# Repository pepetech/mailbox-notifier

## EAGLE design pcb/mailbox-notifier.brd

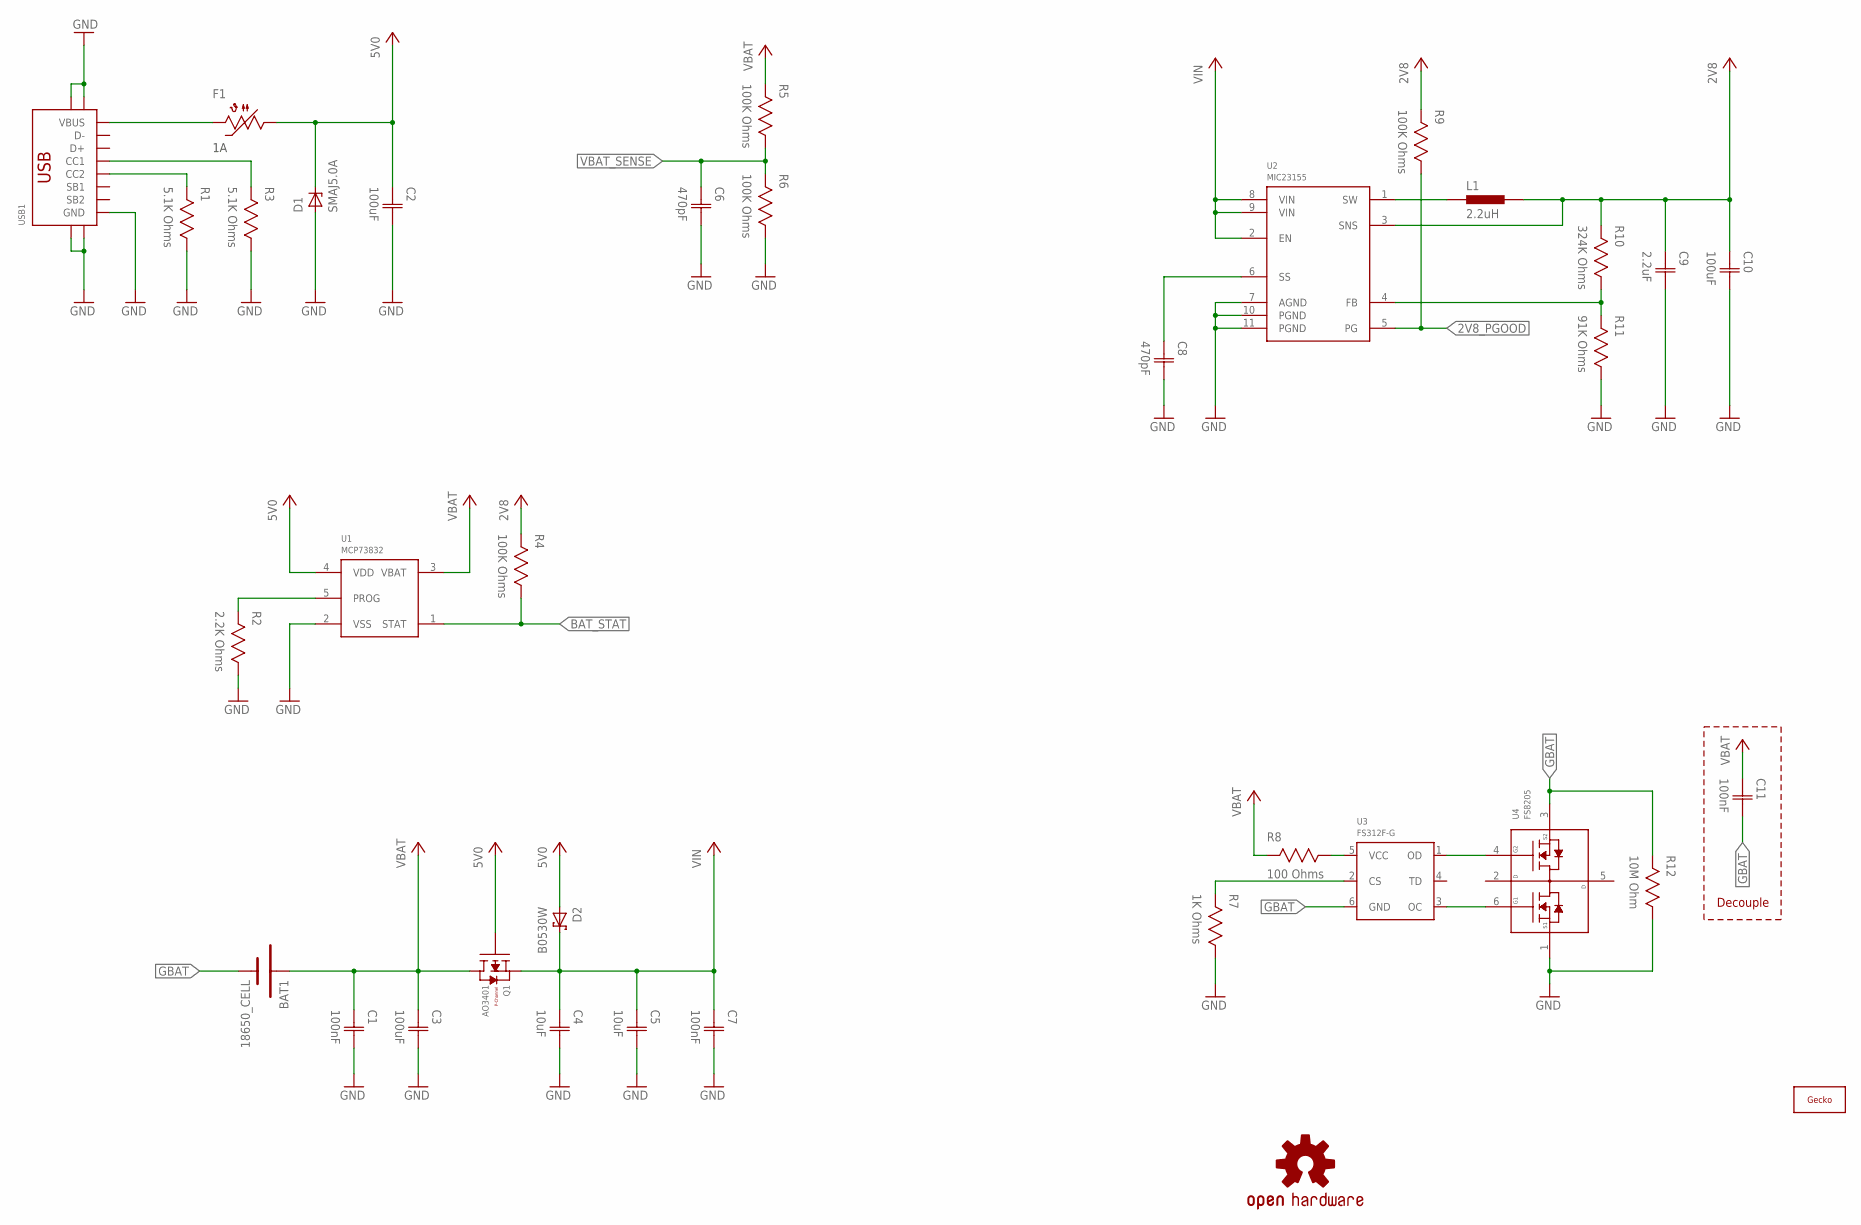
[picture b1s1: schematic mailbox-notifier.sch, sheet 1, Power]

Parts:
BAT1: 18650_CELL; 18650
C1, C7, C11: 100nF; CAP0603
C2, C3, C10: 100uF; CAP1206
C4, C5: 10uF; CAP0603
C6, C8: 470pF; CAP0603
C9: 2.2uF; CAP0603
D1: SMAJ5.0A; DO214AC
D2: B0530W; SOD-123
F1: 1A Hold; 1206
L1: 2.2uH; IND0805
LOGO1: GECKO-14MM; GECKO_14MM
LOGO2: OSHW-LOGOM; OSHW-LOGO-M
Q1: AO3401; SOT23
R1, R3: 5.1K Ohms; RES0603
R2: 2.2K Ohms; RES0603
R4, R5, R6, R9: 100K Ohms; RES0603
R7: 1K Ohms; RES0603
R8: 100 Ohms; RES0603
R10: 324K Ohms; RES0603
R11: 91K Ohms; RES0603
R12: 10M Ohm; RES0603
U1: MCP73832; SOT23-5
U2: MIC23155; DFN10
U3: FS312F-G; SOT23-6
U4: FS8205; SOT23-6
USB1: USB-C-16P-SMD-FLAT-SIDE-TYPE-2

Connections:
2V8: C9.1 (C1), C10.1 (C1), L1.2, R4.2, R9.2, R10.2, U2.3 (SNS); also elsewhere on the board
2V8_PGOOD: R9.1, U2.5 (PG); also elsewhere on the board
5V0: C2.1 (C1), D1.C, D2.A, F1.1, Q1.1 (G), U1.4 (VDD)
BAT_STAT: R4.1, U1.1 (STAT); also elsewhere on the board
GBAT: BAT1.-, C11.2 (C2), R12.2, U3.6 (GND), U4.3 (S2)
GND: C1.2 (C2), C2.2 (C2), C3.2 (C2), C4.2 (C2), C5.2 (C2), C6.2 (C2), C7.2 (C2), C8.2 (C2), C9.2 (C2), C10.2 (C2), D1.A, R1.1, R2.1, R3.1, R6.1, R7.1, R11.1, R12.1, U1.2 (VSS), U2.7 (AGND), U2.10 (PGND), U2.11 (PGND), U4.1 (S1), USB1.A1/B12 (GND), USB1.B1/A12 (GND), USB1.SHIELD@0 (SHIELD), USB1.SHIELD@1 (SHIELD), USB1.SHIELD@2 (SHIELD), USB1.SHIELD@3 (SHIELD); also elsewhere on the board
unnamed: R1.2, USB1.B5 (CC2)
unnamed: F1.2, USB1.A4/B9 (VBUS), USB1.B4/A9 (VBUS)
unnamed: R3.2, USB1.A5 (CC1)
unnamed: R2.2, U1.5 (PROG)
unnamed: L1.1, U2.1 (SW)
unnamed: R10.1, R11.2, U2.4 (FB)
unnamed: C8.1 (C1), U2.6 (SS)
unnamed: U3.3 (OC), U4.6 (G1)
unnamed: U3.1 (OD), U4.4 (G2)
unnamed: R8.1, U3.5 (VCC)
unnamed: R7.2, U3.2 (CS)
VBAT: BAT1.+, C1.1 (C1), C3.1 (C1), C11.1 (C1), Q1.3 (D), R5.2, R8.2, U1.3 (VBAT)
VBAT_SENSE: C6.1 (C1), R5.1, R6.2; also elsewhere on the board
VIN: C4.1 (C1), C5.1 (C1), C7.1 (C1), D2.C, Q1.2 (S), U2.2 (EN), U2.8 (VIN), U2.9 (VIN)

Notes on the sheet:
Decouple

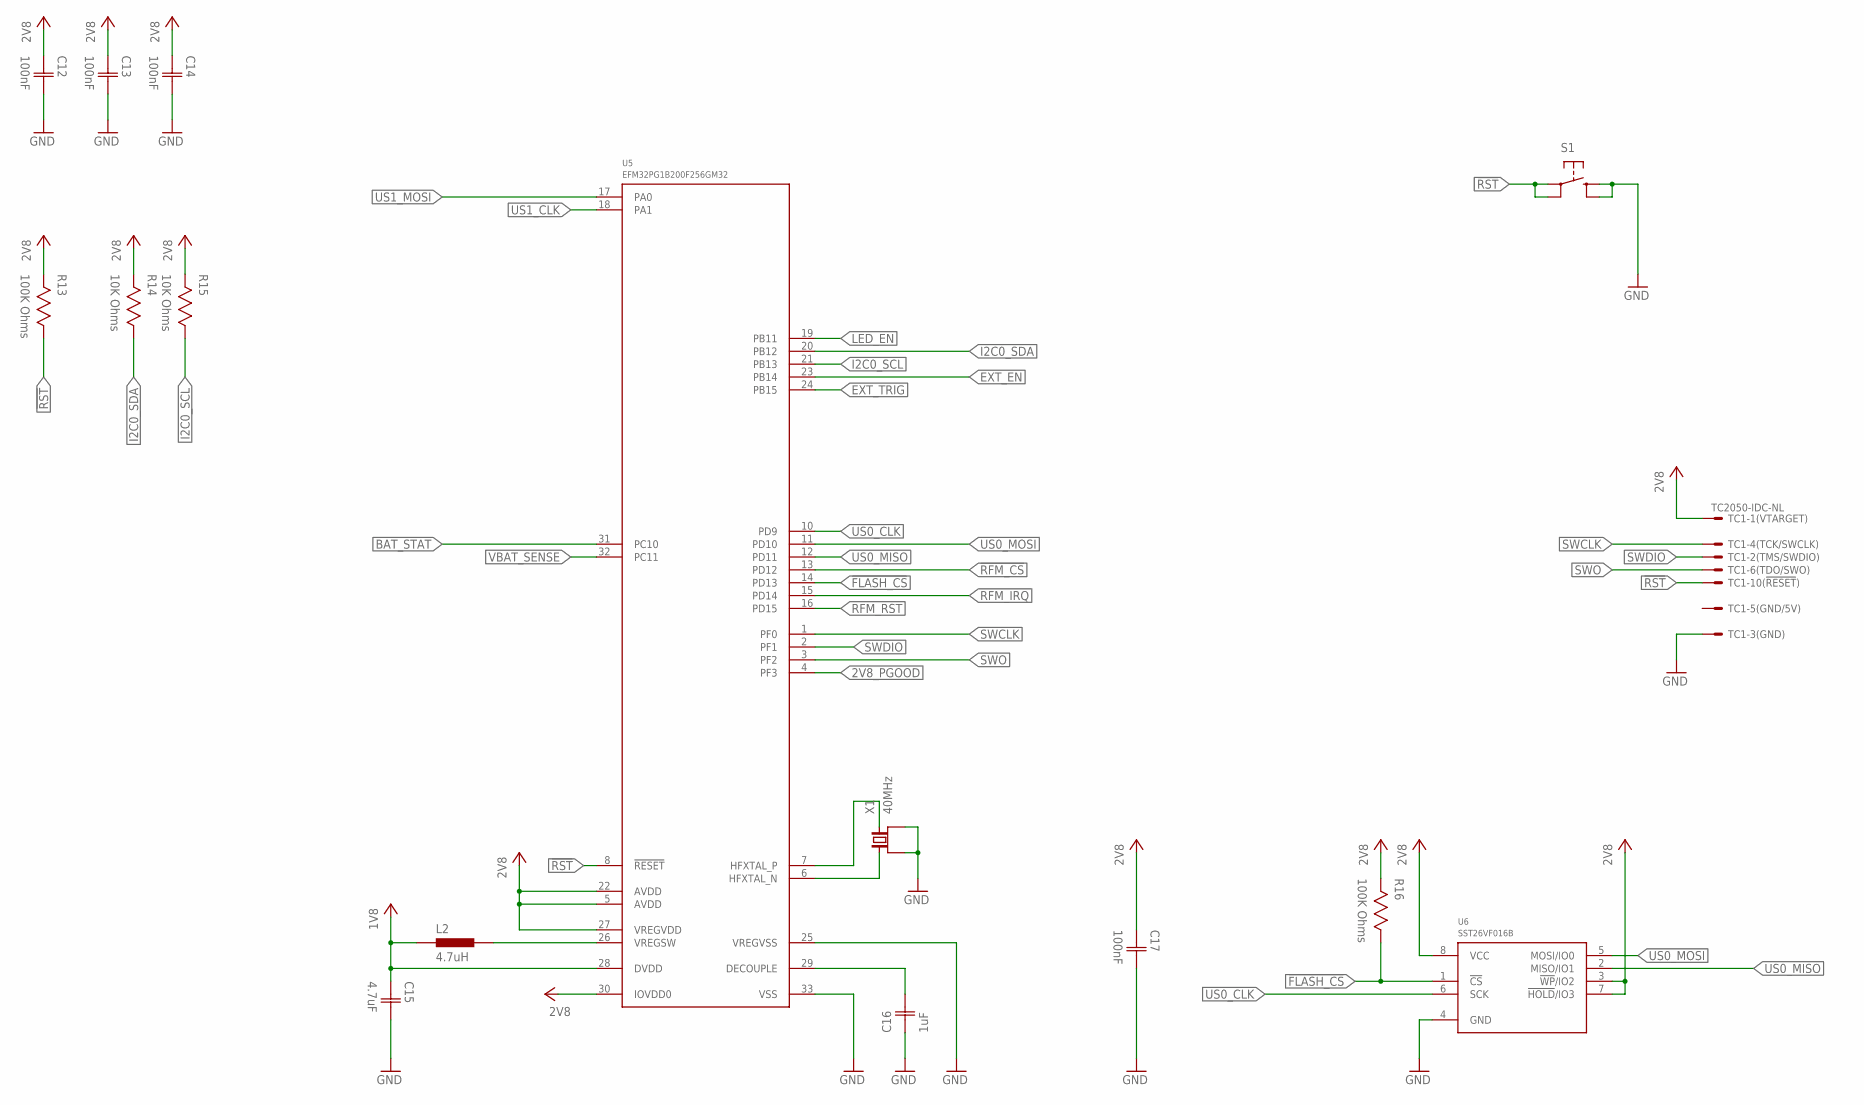
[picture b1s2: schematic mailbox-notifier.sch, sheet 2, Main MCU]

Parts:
C12, C13, C14, C17: 100nF; CAP0603
C15: 4.7uF; CAP0603
C16: 1uF; CAP0603
L2: 4.7uH; IND0603
R13, R16: 100K Ohms; RES0603
R14, R15: 10K Ohms; RES0603
S1: TAC_SWITCHSMD; TAC_SW_SMD_RESET
TC1: TC2050-IDC-NL
U5: EFM32PG1B200F256GM32; QFN32_0.5P
U6: SST26VF016B; WSOIC8
X1: 40MHz; 4-SMD-3225

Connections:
1V8: C15.1 (C1), L2.1, U5.28 (DVDD)
2V8: C12.1 (C1), C13.1 (C1), C14.1 (C1), C17.1 (C1), R13.2, R14.2, R15.2, R16.2, TC1.1, U5.5 (AVDD), U5.22 (AVDD), U5.27 (VREGVDD), U5.30 (IOVDD0), U6.3 (!WP!/IO2), U6.7 (!HOLD!/IO3), U6.8 (VCC); also elsewhere on the board
2V8_PGOOD: U5.4 (PF3); also elsewhere on the board
!FLASH_CS: R16.1, U5.14 (PD13), U6.1 (!CS!)
!RFM_CS: U5.13 (PD12); also elsewhere on the board
!RST: R13.1, S1.1, S1.2, TC1.10, U5.8 (!RESET)
BAT_STAT: U5.31 (PC10); also elsewhere on the board
EXT_EN: U5.23 (PB14); also elsewhere on the board
EXT_TRIG: U5.24 (PB15); also elsewhere on the board
GND: C12.2 (C2), C13.2 (C2), C14.2 (C2), C15.2 (C2), C16.1 (C1), C17.2 (C2), S1.3, S1.4, TC1.3, U5.25 (VREGVSS), U5.33 (VSS), U6.4 (GND), X1.1 (GND), X1.3 (GND); also elsewhere on the board
I2C0_SCL: R15.1, U5.21 (PB13); also elsewhere on the board
I2C0_SDA: R14.1, U5.20 (PB12); also elsewhere on the board
LED_EN: U5.19 (PB11); also elsewhere on the board
unnamed: U5.6 (HFXTAL_N), X1.2 (1)
unnamed: U5.7 (HFXTAL_P), X1.4 (2)
unnamed: L2.2, U5.26 (VREGSW)
unnamed: C16.2 (C2), U5.29 (DECOUPLE)
RFM_IRQ: U5.15 (PD14); also elsewhere on the board
RFM_RST: U5.16 (PD15); also elsewhere on the board
SWCLK: TC1.4, U5.1 (PF0)
SWDIO: TC1.2, U5.2 (PF1)
SWO: TC1.6, U5.3 (PF2)
US0_CLK: U5.10 (PD9), U6.6 (SCK); also elsewhere on the board
US0_MISO: U5.12 (PD11), U6.2 (MISO/IO1); also elsewhere on the board
US0_MOSI: U5.11 (PD10), U6.5 (MOSI/IO0); also elsewhere on the board
US1_CLK: U5.18 (PA1); also elsewhere on the board
US1_MOSI: U5.17 (PA0); also elsewhere on the board
VBAT_SENSE: U5.32 (PC11); also elsewhere on the board

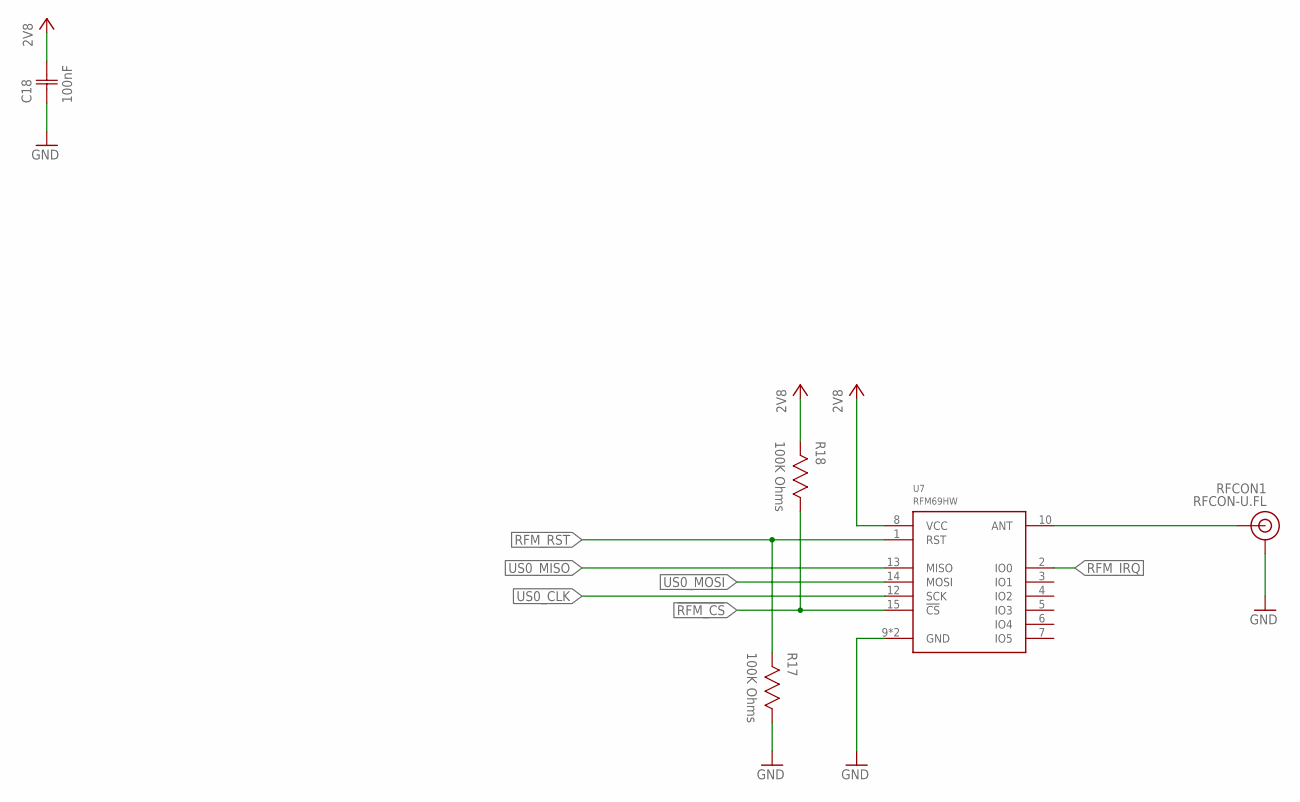
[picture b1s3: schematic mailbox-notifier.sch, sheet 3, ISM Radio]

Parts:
C18: 100nF; CAP0603
R17, R18: 100K Ohms; RES0603
RFCON1: RFCON-U.FL; U.FL
U7: RFM69HW; RFM69XW-XXXS2

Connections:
2V8: C18.2 (C2), R18.2, U7.8 (VCC); also elsewhere on the board
!RFM_CS: R18.1, U7.15 (!CS); also elsewhere on the board
GND: C18.1 (C1), R17.1, RFCON1.P$1 (GND), RFCON1.P$2 (GND), U7.9 (GND), U7.11 (GND); also elsewhere on the board
unnamed: RFCON1.P$3 (SIGNAL), U7.10 (ANT)
RFM_IRQ: U7.2 (IO0); also elsewhere on the board
RFM_RST: R17.2, U7.1 (RST); also elsewhere on the board
US0_CLK: U7.12 (SCK); also elsewhere on the board
US0_MISO: U7.13 (MISO); also elsewhere on the board
US0_MOSI: U7.14 (MOSI); also elsewhere on the board

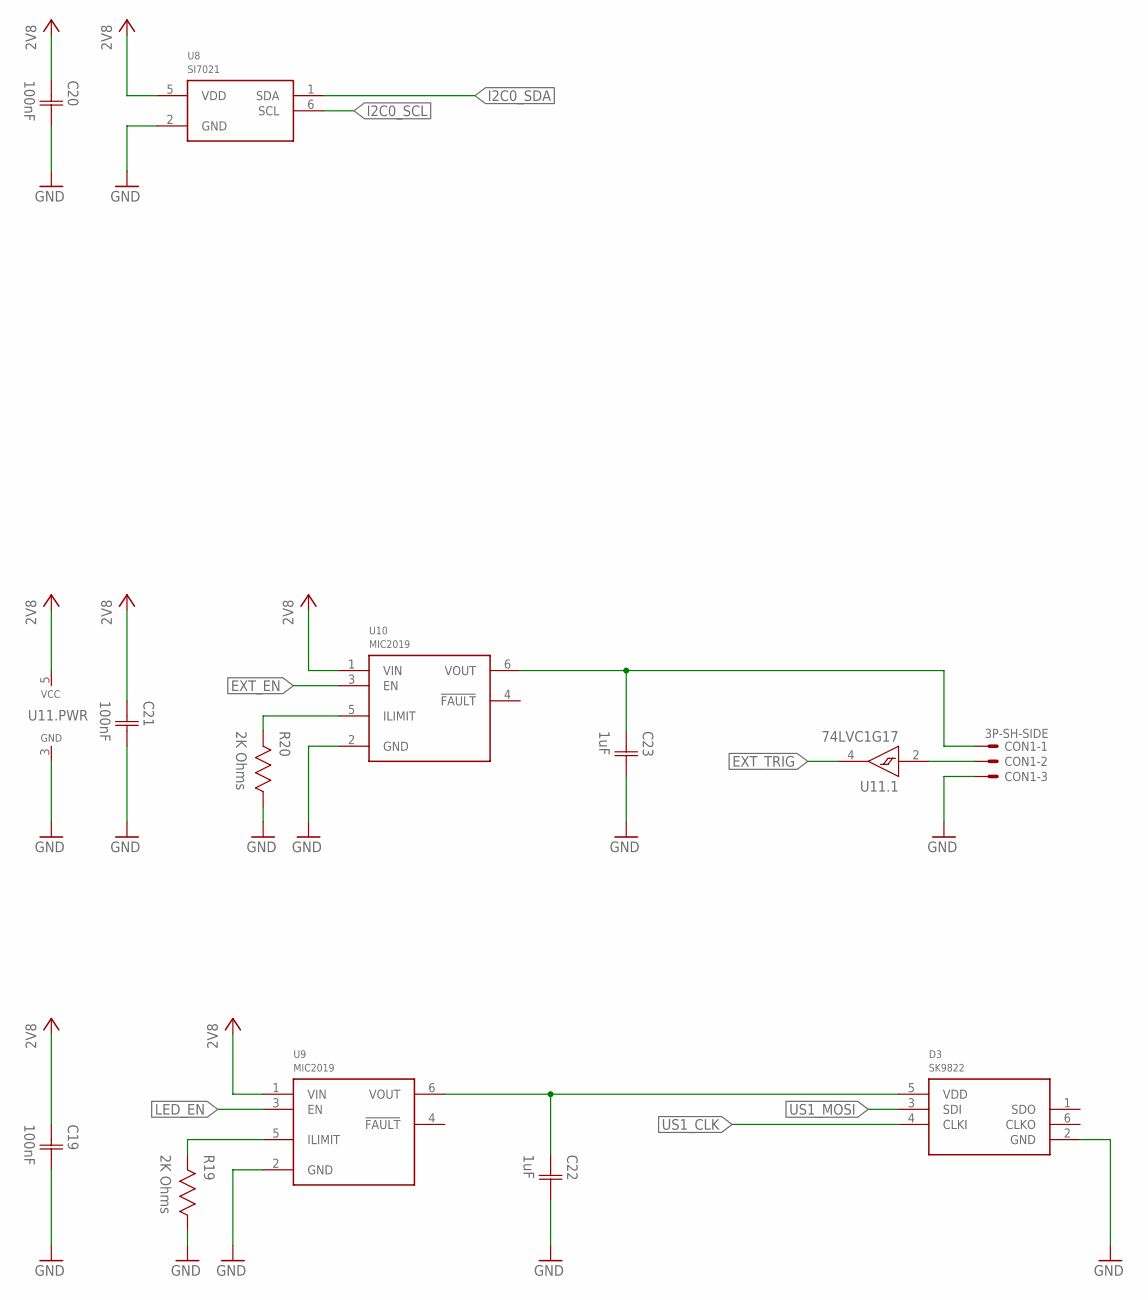
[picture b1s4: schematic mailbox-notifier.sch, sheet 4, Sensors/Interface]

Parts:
C19, C20, C21: 100nF; CAP0603
C22, C23: 1uF; CAP0603
CON1: 3P-SH-SIDE; SH-03-SIDE
D3: SK9822; 2020
R19, R20: 2K Ohms; RES0603
U8: SI7021; DFN6
U9, U10: MIC2019; SOT23-6
U11: 74LVC1G17; SC70-5

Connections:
2V8: C19.1 (C1), C20.1 (C1), C21.1 (C1), U8.5 (VDD), U9.1 (VIN), U10.1 (VIN), U11.5 (VCC); also elsewhere on the board
EXT_EN: U10.3 (EN); also elsewhere on the board
EXT_TRIG: U11.4 (Y); also elsewhere on the board
GND: C19.2 (C2), C20.2 (C2), C21.2 (C2), C22.2 (C2), C23.2 (C2), CON1.3, D3.2 (GND), R19.1, R20.1, U8.2 (GND), U9.2 (GND), U10.2 (GND), U11.3 (GND); also elsewhere on the board
I2C0_SCL: U8.6 (SCL); also elsewhere on the board
I2C0_SDA: U8.1 (SDA); also elsewhere on the board
LED_EN: U9.3 (EN); also elsewhere on the board
unnamed: R20.2, U10.5 (ILIMIT)
unnamed: CON1.2, U11.2 (A)
unnamed: C23.1 (C1), CON1.1, U10.6 (VOUT)
unnamed: R19.2, U9.5 (ILIMIT)
unnamed: C22.1 (C1), D3.5 (VDD), U9.6 (VOUT)
US1_CLK: D3.4 (CLKI); also elsewhere on the board
US1_MOSI: D3.3 (SDI); also elsewhere on the board

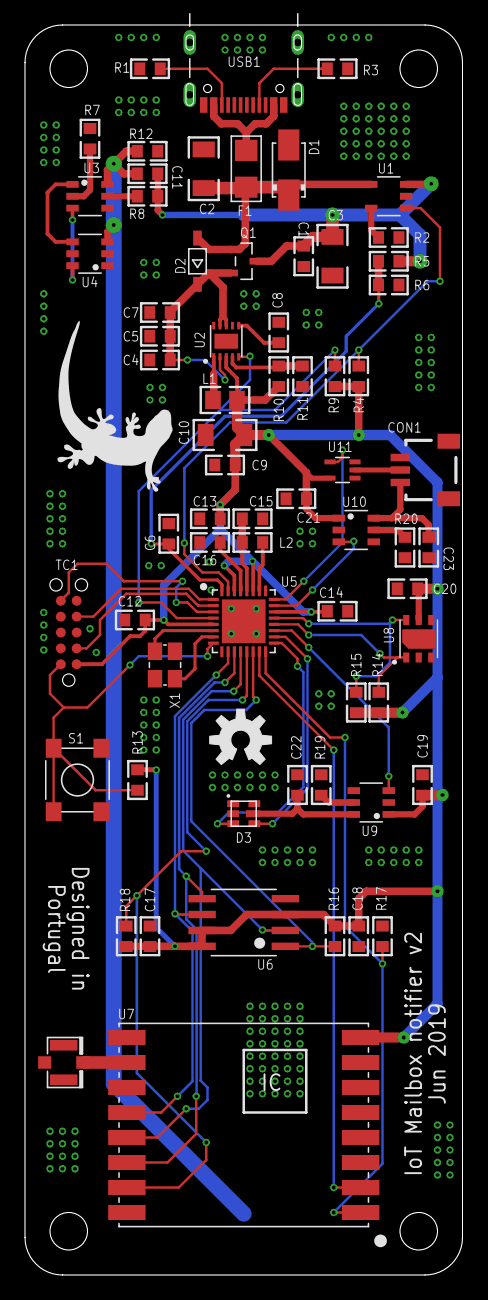
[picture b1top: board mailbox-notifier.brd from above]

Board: 2 copper layers, 35.0 x 100.0 mm, 70 parts (1 on the bottom side), 49 nets.

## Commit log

2019-05-23 Fix Eagle linux layer colors
2019-05-23 PCB Work
2019-05-25 Add power switch to external trigger
2019-05-27 nothing to do
2019-05-31 Finish board Generate gerbers
2019-05-31 Machine gun
2019-06-04 Fix USB C
2019-07-06 Change DRCs
2019-07-24 Change DRCs Change crystal package
2019-07-28 Sync libraries
2019-10-07 Ghanged DRC Generated new gerbers
2019-12-30 Sync library updates Add schematic PDF
